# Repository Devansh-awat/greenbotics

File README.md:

|  |
| :----------------------------------------------------------: |

|  |  |
| :----------------------------------------------------------- | -----------------------------------------------------------: |
| Scan QR to open Github repo                                  |                                Scan QR to open YouTube video |

<div style="font-family: Baskerville; font-size: 28px; text-align: center; font-style: italic;">
    This Incredible Repository
</div>

Welcome to the Greenbotics 2025 repository! This repository contains everything we've worked on over the past ten months, including all our code and resources. You can also use this repository as a complete guide to understand and reconstruct the robot from the ground up.

## Table of Contents

- [The Team](#the-team)
- [The Challenge](#the-challenge)
  - [Our Vision](#our-vision)
  - [Skills We Learned](#skills-we-learned)
- [Photos of our Robot](#photos-of-our-robot)
- [Robot Performance Video](#robot-performance-video)
- [Mobility Management](#mobility-management)
  - [Powertrain](#powertrain)
  - [Steering System](#steering-system)
  - [Chassis](#chassis)
  - [Code for mobility components](#code-for-mobility-components)
- [Power and Sense Management](#power-and-sense-management)
  - [LiPo battery](#lipo-battery)
  - [Raspberry Pi](#raspberry-pi)
  - [Voltage Converter](#voltage-converter)
  - [Printed Circuit Board (PCB)](#printed-circuit-board-pcb)
  - [Camera](#camera)
  - [IMU](#imu)
  - [Distance Sensor](#distance-sensor)
  - [Multiplexer](#multiplexer)
  - [Code for sensors](#code-for-sensors)
- [Obstacle Management](#obstacle-management)
  - [Open Challenge Navigation Algorithm](#open-challenge-navigation-algorithm)
    - [Potential improvements in Open Navigation Algorithm](#potential-improvements-in-open-navigation-algorithm)
  - [Obstacle Challenge Navigation Algorithm](#obstacle-challenge-navigation-algorithm)
    - [Potential improvements in Obstacle Navigation Algorithm](#potential-improvements-in-obstacle-navigation-algorithm)
- [Engineering Factors](#engineering-factors)
  - [Design evolution](#design-evolution)
  - [From Nationals to Internationals!](#from-nationals-to-internationals)
- [Robot construction guide](#robot-construction-guide)
  - [1: Print the 3D parts](#1-print-the-3d-parts)
  - [2: Assemble the steering and drive train](#2-assemble-the-steering-and-drive-train)
  - [3: Attach the 3D mounts](#3-attach-the-3d-mounts)
  - [4: Fabricate the PCB](#4-fabricate-the-pcb)
  - [5: Soldering the electronics and gradual safe startup](#5-soldering-the-electronics-and-gradual-safe-startup)
  - [6: Download the code](#6-download-the-code)
  - [7: Robot stability](#7-robot-stability)
- [Major challenges faced](#major-challenges-faced)
- [How we used Github](#how-we-used-github)
- [Bill of Materials](#bill-of-materials)

# The Team

<p style="text-align:center;">Yes. We did know the camera was on!</p>

---

|  | Devansh<br/>Hi! I’m Devansh doing my second WRO season. Last year I represented India in the RoboMission category coming #25 in Internationals. This year I wanted a new challenge and learn new things. My hobbies are coding and robotics. |
| ------------------------------------------------------------ | ------------------------------------------------------------ |
|  | **Sheel**<br/>**Hi! I'm Sheel. I'm 15, and doing my second WRO season. Last year, our team made it to the International Finals in Robomission Junior. Additionally, I'm learning competitive debate. I also have a dog, and both of us are obsessed with Monkeys.** |
|  | **Rakshith**<br/>**I'm Rakshith, a 9th grader passionate about robotics and aspiring to study engineering in Germany. I love building drones, experimenting with sensors. I also have 3 dogs, and two of them live with my grandparents in Hyderabad.** |
|  | **Paresh Gambhava**<br/>**Mr. Paresh Gambhava is our chief coach from The Robotronics Club Ahmedabad. He is a robotics enthusiast, and electrical engineer by profession. He has vast experience training students for Robotics competition and projects.** |

# The Challenge

The [Future Engineer Challenge](https://wro-association.org/wp-content/uploads/WRO-2025-Future-Engineers-Self-Driving-Cars-General-Rules.pdf "View the season rulebook") for the 2025 WRO Season involves building an autonomous vehicle that can complete two challenges. The first challenge is the Open Challenge. This challenge involves the robot completing three full laps on the field. The field consists of outer boundary walls, and 4 inner walls that are randomly placed to form a closed rectangle.

The second challenge is the Obstacle Challenge. In the Obstacle Challenge red or green cuboids called Traffic Signs are placed along the course. The robot must complete three laps around the track while making sure to pass the red traffic signs from the left, and the green traffic signs from the right. The Obstacle Challenge also has a dedicated Parking Space. The robot must start and end in the parking space to attain full points. The walls placement is fixed for the Obstacle Challenge.

## Our Vision

With a deep interest in robotics and programming, the WRO Future engineers challenge was a great opportunity for us to work and build a robot together. We had been seeing other teams in our institute work on this problem last year, and it was greatly motivating for us to see them work. Having represented India in last years WRO RoboMission, we were excited to participate in new category and learn new things.

## Skills We Learned

**Technical Skills:**

- 3D printing and design
- PCB design and creation
- Raspberry Pi programming
- Computer vision and camera programming
- Hardware integration

**Soft Skills:**

- Teamwork
- Problem-solving
- Not go crazy when the robot doesn’t behave as expected !!!

# Photos of our Robot

We designed our robot with Raspberry Pi 5 as the main brain of the car. Raspberry Pi 5 had pre-integrations with the camera allowing us to use faster smarter image procesing algorithms which is critical in this robots design.
Having spent a lot of time working on LEGO-based hardware in the 2024 season, we chose to use many LEGO parts for our Robot's Hardware.  However the robot also uses a Raspberry Pi, Raspberry Pi camera, and other off the shelf electronic components.

|                           Top view                           |                         Bottom view                          |
| :----------------------------------------------------------: | :----------------------------------------------------------: |
|  |  |

|                          Front view                          |                          Rear view                           |
| :----------------------------------------------------------: | :----------------------------------------------------------: |
|  |  |

|                          Left view                           | Right view                                                   |
| :----------------------------------------------------------: | ------------------------------------------------------------ |
|  |  |

# Robot Performance Video

This playlist consists of 3 videos that show our robot's construction, open challenge run as well as obstacle challenge run.

|  |  <br />Scan QR code to open in YouTube |
| ------------------------------------------------------------ | ------------------------------------------------------------ |

---

# Mobility Management

Our robot's mobility system is designed around a LEGO-based chassis that balances ease of assembly with reliable performance. We selected a LEGO EV3 Medium Motor for propulsion due to its compatibility with our modular design approach, delivering 240-250 RPM at 9V through a differential drivetrain that enables smooth turning by allowing wheels to rotate at different speeds. For precise steering control, we integrated an SG90 servo motor with a custom 3D-printed mount that connects to our LEGO chassis. The TB6612FNG motor driver manages power delivery and speed control, while all components are securely mounted to our LEGO framework using standard connectors and custom PCB integration. This design prioritizes modularity and maintainability while providing the torque and precision needed for autonomous navigation challenges.

## Powertrain

### Motor

We chose to use a standard LEGO EV3 Medium Motor, as it easily integrates with the lego chassis and lego axle. This motor also embeds an encoder which could be used if required. However, the standard Lego connector doesn’t directly connect to our motor driver, therefore we identified the pinout of the LEGO motor and directly connected the wires to the motor driver. The pinout diagram of Lego EV3 motor is shown below

---
<table>
  <tr>
    <td width="50%" style="text-align: left;">
      
    </td>
    <td width="50%" style="text-align: left; vertical-align: top;">
      <h3>Specifications:</h3>
      <li>Name: LEGO EV3 Motor</li>
      <li>Voltage: 9V</li>
      <li>No Load Speed: 240 to 250 RPM</li>
      <li>Weight: 40g</li>
      <li>Encoder resolution: 1°</li>
    </td>
  </tr>
</table>

---

**Potential improvements:**

- Use the built-in encoder for more accurate movement and turns of the robot. Using the encoder allows for precise and accurate movements, helping in complex tasks like parking.

- Consider exploring more powerful non-Lego geared motors that are

    -Compact and lightweight

    -More powerful

    -Cheaper

### Drivetrain

Our EV3 motor is connected to a Lego axle that drives a gear connected to a Lego differential, which splits torque between two wheels. The differential lets both wheels rotate at different speeds when turning, thereby reducing the friction at each wheel, and making turns smoother. We used lego wheels as they are compatible with lego axle used for the chassis. We experimented with a wide variety of Lego wheels for the robot. Increasing the size of the rear wheel increased the robot speed almost linearly proportional to the wheel diameter. Increasing the width of the front tyres caused the robot to skid during turns, hence the front wheels are narrower to make smooth turns. The rear wheels are wider to provide sufficient friction to the vehicle.

**Potential Improvements**

- Explore alternative differential gear mechanisms to avoid the wheels slipping, especially on the smooth surface of the mat.
- Explore options for front wheels with vertical treads as the Lego narrow wheels do not have tread.

### Motor Driver

To control the current received by the motor and to control the speed of the drive motor, we utilized a SparkFun Dual TB6612FNG motor driver. The motor driver is connected to our PCB, and receives signals from the Raspberry Pi.

<table>
  <tr>
    <td width="50%" style="text-align: left;">
      
    </td>
    <td width="50%" style="text-align: left; vertical-align: top;">
      <h3>Specifications:</h3>
      <li>Name: TB6612FNG</li>
      <li>Power Supply Voltage: 15V (Max)</li>
      <li>Average Output current: 1.2A</li>
      <li>Peak Output current: 3.2A</li>
      <li>Standby control to save power</li>
      <li>Built-in thermal shutdown circuit</li>
    </td>
  </tr>
</table>

**Potential Improvements:**

- Explore motor driver that can output higher currents, if we upgrade existing motors to higher performance motors

## Steering System

For our steering mechanism, we needed a design that was precise. Like all other aspects of our robot’s design, our first choice was to use a Lego based mechanism. Ackerman steering is a popular choice in automobiles, as the front inner wheel turns more than the front outer wheel, thereby reducing skid. However it was complicated to build it. We first tried the simpler parallel steering mechanism and it turned out to be pretty good for our robot, so we didn't consider Ackerman steering.

The steering could have been driven by any encoder based motor (such as a spike prime small motor) as a makeshift servo motor. The problem was, that while any Lego motor would have been both highly precise and easy to integrate, even the smallest motor was too bulky and required integration with motor driver.

Therefore, we decided to use an off the shelf servo motor, which was not only small but can be driven directly by Raspberry Pi's output port. To integrate it with our Lego based design, we 3D printed a custom servo mount which could be attached with Lego screws to the front of the chassis directly behind the front wheel, while simultaneously hot gluing the servo horn to 3D printed component that couples the horn to the axle of the front wheels.

**Potential Improvements:**

- Explore if Ackerman steering provides better maneuverability.

### Servo Motor

Our steering system is centered around the SG90 servo motor, which provides precise angular control, making it highly suitable for steering applications where accuracy is essential. Unlike standard DC motors, the SG90 has a built-in feedback mechanism that allows it to hold a commanded angle reliably without additional sensors. Despite its compact size, it delivers sufficient torque to handle the demands of turning the steering mechanism, ensuring stability.

<table>
  <tr>
    <td width="50%" style="text-align: left;">
      
    </td>
    <td width="50%" style="text-align: left; vertical-align: top;">
      <h3>Specifications:</h3>
      <li>Name: SG90</li>
      <li>Operating voltage: 3.0V - 7.2V</li>
      <li>Weight: 9g</li>
    </td>
  </tr>
</table>

<table>
  <tr>
    <td width="50%" style="text-align: left;">
      
    </td>
    <td width="50%" style="text-align: left; vertical-align: top;">
      <h3>Servo mount</h3>
      <li>To connect the servo motor to our robot, we designed and 3D printed a custom Servo Mount</li>
      <li>A diagram of our servo mount is shown to the left.</li>
      <li>A 3D Printable file is provided in the models folder.</li>
    </td>
  </tr>
</table>

**Challenges:**

For a brief period, we used an MG90 servo motor instead of our current SG90 motor. An MG90 has metal gears instead of plastic gears, which we believed would make it more reliable. However, the MG90 gears broke in one of our test runs, and we reverted back to the SG90

**Potential Improvements:**

- 3D print the servo horn to directly connect to the chassis without gluing

## Chassis

When starting this project, we realized that the bulk of our effort would go into building autonomous driving software. As we wanted to spend more time on software, and had already spent a considerable amount of time using Lego hardware for our 2024 Robomission challenge, we **custom designed** the base chassis from elementary Lego parts and rest of the chassis with **3D printed parts**.

This approach has many benefits, the primary one being ease of integration. Lego parts can easily be snapped on and off, making chassis development far easier and less time consuming. Making changes to a non-Lego chassis would have meant that each time we wanted to make a change to our chassis, we would have to make new 3D prints, increasing time, cost, waste and materials used.

All sensors like the camera, ultrasonic sensors and TOF sensors are attached to the base chassis with 3D printed mounts. This provides robust attachment of the the sensors to the main body. The prototype was built with hot gluing these sensors to the body but this wasn't robust and would come off.

|  |  |
| ------------------------------------------------------------ | ------------------------------------------------------------ |
|  |  |

|  |
| :----------------------------------------------------------: |

**Potential Improvements:**

- Despite being mounted on a thick 3D-printed mount, the camera vibrates when the robot is in motion, blurring the image. The mount could be coupled with vibration damping material.
- Lightweight suspension can be added to the chassis to enhance stability.
- The Raspberry Pi's cooling fan can be covered with a custom 3D printed cover to avoid dust and debris getting into the fan.
- The current 3D printed parts are printed with 100% infill for robustness but it increases the weight. We could explore an optimum infill that gives the minimum strength at the lowest possible weight.

## Code for mobility components

### Motor Control

Controls the drive motor speed and direction using PWM (pulse-width modulation) signals sent to the TB6612FNG motor driver.

#### Initialization

```python
def initialize():
    """Initializes the DC motor driver and PWM."""
    global gpio_handle, motor_pwm
    try:
        gpio_handle = lgpio.gpiochip_open(0)
        lgpio.gpio_claim_output(gpio_handle, config.AIN1_PIN)
        lgpio.gpio_claim_output(gpio_handle, config.AIN2_PIN)
        lgpio.gpio_claim_output(gpio_handle, config.STBY_PIN)
        
        motor_pwm = HardwarePWM(
            pwm_channel=config.MOTOR_PWM_CHANNEL,
            hz=config.MOTOR_PWM_FREQ,
            chip=config.MOTOR_PWM_CHIP,
        )
        motor_pwm.start(0)
        print("INFO: Motor Initialized.")
        return True
    except Exception as err:
        print(f"FATAL: Motor failed to initialize: {err}")
        return False
```

**Explanation:** We set up the GPIO pins that control the motor direction (AIN1, AIN2) and standby mode (STBY). We also initialize the PWM signal that controls motor speed.

#### Motor Control Functions

```python
def forward(speed):
    """Drives the motor forward at a given speed."""
    if gpio_handle:
        lgpio.gpio_write(gpio_handle, config.STBY_PIN, 1)  # Enable motor
        lgpio.gpio_write(gpio_handle, config.AIN1_PIN, 1)  # Forward direction
        lgpio.gpio_write(gpio_handle, config.AIN2_PIN, 0)
        _set_speed(speed)  # Set speed 0-100

def reverse(speed):
    """Drives the motor in reverse at a given speed."""
    if gpio_handle:
        lgpio.gpio_write(gpio_handle, config.STBY_PIN, 1)  # Enable motor
        lgpio.gpio_write(gpio_handle, config.AIN1_PIN, 0)  # Reverse direction
        lgpio.gpio_write(gpio_handle, config.AIN2_PIN, 1)
        _set_speed(speed)

def brake():
    """Brakes the motor by shorting its terminals."""
    if gpio_handle:
        lgpio.gpio_write(gpio_handle, config.STBY_PIN, 1)
        lgpio.gpio_write(gpio_handle, config.AIN1_PIN, 1)  # Both pins high = brake
        lgpio.gpio_write(gpio_handle, config.AIN2_PIN, 1)
        _set_speed(0)
```

**Explanation:** These functions control motor direction by setting the AIN1 and AIN2 pins. Forward sets AIN1=1 and AIN2=0. Reverse does the opposite. Brake sets both to 1, which stops the motor quickly.

---

### Servo Steering

Controls the steering servo angle using PWM signals. The servo position determines the steering direction.

#### Initialization

```python
def initialize():
    """Initializes the servo motor PWM."""
    global servo_pwm
    
    for attempt in range(1, 6):  # Try up to 5 times
        try:
            servo_pwm = HardwarePWM(
                pwm_channel=config.SERVO_PWM_CHANNEL,
                hz=config.SERVO_PWM_FREQ,
                chip=config.SERVO_PWM_CHIP,
            )
            servo_pwm.start(0)
            set_angle(0.0)  # Center the servo
            time.sleep(0.5)
            print("INFO: Servo Initialized.")
            return True
        except PermissionError as err:
            print(f"WARNING: Servo PWM permission denied (attempt {attempt}/5): {err}")
            time.sleep(0.1 * attempt)
    
    print("FATAL: Servo failed to initialize after 5 attempts")
    return False
```

**Explanation:** We initialize the PWM signal for the servo. The servo needs a specific frequency (50 Hz) and pulse width to set its angle. We center it at 0 degrees during startup.

#### Servo Angle Control

```python
def set_angle(input_angle: float):
    """Sets the servo to a specific angle (-45 to +45 degrees)."""
    if servo_pwm is None:
        return
    
    # Clamp angle to safe limits
    clamped_angle = max(-45, min(45, input_angle))
    
    # Convert angle to PWM duty cycle
    # Servo expects 1-2ms pulse width at 50Hz frequency
    pulse_width_ms = 1.5 + (clamped_angle / 90) * 0.5
    duty_cycle = (pulse_width_ms / 20) * 100
    
    servo_pwm.change_duty_cycle(duty_cycle)
```

**Explanation:** Servo motors work by receiving a PWM signal with a specific pulse width. A 1.5ms pulse = center (0°), 1ms = full left (-90°), 2ms = full right (+90°). We calculate the duty cycle based on the desired angle.

# Power and Sense Management

Our robot uses a Raspberry Pi 5 to process data from several sensors. We use ultrasonic and TOF sensors for distance, an IMU for orientation, and a camera for autonomous driving. A Li-Po battery powers the entire system.

## LiPo battery

Our robot uses a Bonka 11.1V 2200mAh LiPo battery, commonly found in drones and quadcopters. We chose this battery because its compact form factor fits in the narrow space beneath the chassis. Mounting the heavy battery low in the robot lowers the center of mass, which improves stability.

<table>
  <tr>
    <td width="50%" style="text-align: left;">
      
    </td>
    <td width="50%" style="text-align: left; vertical-align: top;">
      <h3>Specifications:</h3>
      <li>Maximum Voltage: 12.6V </li>
      <li>Nominal Voltage: 11.1V </li>
      <li>Capacity: 2200mAh</li>
      <li>Discharge Current: 35C</li>
      <li>Weight: 175g</li>
    </td>
  </tr>
</table>

---
**Potential Improvements**

- Implement a battery level indicator
- Explore if a Lithium-Ion battery is available in the required form factor, as it

    - Is safer

    - Has more charge cycles

    - Doesn't require a complex charger that a LiPo requires
    
    - Can be easily removed and replaced with another charged battery
---
## Raspberry Pi

The heart of our robot is the Raspberry Pi 5 microcomputer. It processes inputs from our distance sensors, runs image processing algorithms on the live camera feed and controls the motors to drive the robot to achieve its desired goals.

We chose this particular model as it seamlessly integrates with a camera, making it easier to use than similar computers or microcontrollers such as an Arduino or ESP32. Additionally, we also wanted to take advantage of the Raspberry Pi 5 being far more powerful than other processors, allowing us to use newer and improved image processing technologies that deliver more accurate results but may require greater computing power.

**Potential Improvements**

- Use Arduinos and compatible cameras to make this robot much cheaper to design

<table>
  <tr>
    <td width="50%" style="text-align: left;">
      
    </td>
    <td width="50%" style="text-align: left; vertical-align: top;">
      <h3>Specifications:</h3>
      <li>Name: Raspberry Pi 5 </li>
      <li>RAM: 8GB</li>
      <li>Pins: 40</li>
      <li>Input Voltage: 5V</li>
    </td>
  </tr>
</table>

## Voltage Converter

Our battery provides 12V, but our Raspberry Pi requires 5V and our motor requires 9V. To supply these lower voltages safely, we used a XY-3606 step-down (buck) voltage converter.

**Potential Improvements**

- Use a linear converter to reduce costs
- Use a buck converter that is more efficient and provides more power at different voltages. This ensures that all components running at all voltages can be used

<table>
  <tr>
    <td width="50%" style="text-align: left;">
      
    </td>
    <td width="50%" style="text-align: left; vertical-align: top;">
      <h3>Specifications:</h3>
      <li>Name: XY-3606 </li>
      <li>Working voltage: DC 9V–36V</li>
      <li>Output voltage: 5.2V</li>
    </td>
  </tr>
</table>

## Printed Circuit Board (PCB)

In our first draft of the robot, there were many criss-crossing wires between many different components. A lack of clean arrangement for the wires made the robot very messy to handle. During practice runs, wires would routinely get loose, making it difficult to troubleshoot errors.

To solve this, we designed a PCB which cleanly connected all of our components together, making the robot far cleaner and reliable.

Here is a comparison showing our robot before and after the PCB

| Before                                                       | After                                                        |
| ------------------------------------------------------------ | ------------------------------------------------------------ |
|  |  |

<table>
  <tr>
    <td width="50%" style="text-align: left;">
      
    </td>
    <td width="50%" style="text-align: left; vertical-align: top;">
      <h3>PCB</h3>
      <li>This is our PCB image with all components mounted</li>
      <li>The 'models/PCB' folder contains the files required to print this PCB</li>
    </td>
  </tr>
</table>

## Camera

For image detection, we are using the Raspberry Pi Camera Module 3. This uses a CMOS sensor, the Sony IMX708. Apart from its ease of integration with the Raspberry Pi, the Camera module 3 has autofocus, wide-angle and low-light performance, all of which are very useful in a competition setting.

We explored few other alternatives as well. The Raspberry Pi AI camera provides built in detection for many objects, but has a limited Field Of View which didn't work for our requirements. The Raspberry Pi HQ camera though bulky comes with a standard CS mount that allowed us to mount different fish eye lenses. A fish eye lens camera provides a much larger Field Of View (160° - 180°) even when mounted in the front on a straight mount at 10cm height. This allows us to cut off the field view above the black walls making the robot resilient to off field objects. However the image is distorted towards the edges and tuning the robot to detect objects proved difficult for us.

<table>
  <tr>
    <td width="50%" style="text-align: left;">
      
    </td>
    <td width="50%" style="text-align: left; vertical-align: top;">
      <h3>Specifications:</h3>
      <li>Name: Camera Module 3 </li>
      <li>Resolution: 11.9 megapixels</li>
      <li>Horizontal/vertical: 4608 × 2592 pixels</li>
      <li>Autofocus, Wide-angle and Low-light performance</li>
    </td>
  </tr>
</table>

**Potential Improvements**

- Use an alternative wide angle AI camera to process data on the camera itself. This will reduce processing load on the Raspberry Pi.
- Attempt to resolve tuning issues with fish eye camera to ignore off field objects.

## IMU

Our robot uses the BNO055 IMU (Inertial Measurement Unit) to help it maintain direction when moving straight, and to make turns more accurate. The BNO055 combines data from an accelerometer, gyroscope, and magnetometer to provide absolute orientation, which reduces drift and allows the robot to correct its heading in real time.

<table>
  <tr>
    <td width="50%" style="text-align: left;">
      
    </td>
    <td width="50%" style="text-align: left; vertical-align: top;">
      <h3>Specifications:</h3>
      <li>I2C Address: 0x28 </li>
      <li>Gyroscope: Range ±125°/s to ±2000°/s</li>
      <li>Accelerometer: Range ±2g, ±4g, ±8g, ±16g</li>
    </td>
  </tr>
</table>

**Potential Improvements**

- Move the IMU away from areas of magnetic interference
- Use higher quality IMUs such as the BNO085

## Distance Sensor

Apart from the camera, our robot uses TOF based distance sensors VL53L1X / VL53L8CX and URM09 Ultrasonic sensor to gather inputs. The sensors are mounted on the front, back, left, and right of the robot respectively. The front and back sensors are used to avoid hitting the parking walls. The left and right sensors are used to detect the starting direction for obstacle challenge. They could potentially be used for a surprise rule that may be announced at the competition.

**Reasons for using different sensors**

- Ultrasonic sensors are not affected by strong lighting at competition arenas and are useful to detect objects at larger distance. This is useful for wall detection.
- Some TOF sensors could potentially be affected by strong lighting at competition arenas, but are usually safe over short distances. This is useful for parking.
  - The back sensor is attached to the edge of the rear chassis hence requires min 2cm range.
  - The front sensor is attached to the inner cavity behind the front wheels hence can work with 4cm range.

<table>
  <tr>
    <td width="50%" style="text-align: left;">
      
    </td>
    <td width="50%" style="text-align: left; vertical-align: top;">
      <h3>VL53L1X Specifications:</h3>
      <li>Operating Voltage: 3.3V </li>
      <li>Range: 4cm to 4m</li>
      <li>Resolution: 1mm</li>
    </td>
  </tr>
  <tr>
    <td width="50%" style="text-align: left;">
      
    </td>
    <td width="50%" style="text-align: left; vertical-align: top;">
      <h3>VL53L8CX Specifications:</h3>
      <li>Operating Voltage: 3.2V to 5.5V </li>
      <li>Range: 2cm to 4m</li>
      <li>Resolution: 1mm</li>
    </td>
  </tr>  
  <tr>
    <td width="50%" style="text-align: left;">
      
    </td>
    <td width="50%" style="text-align: left; vertical-align: top;">
      <h3>URM09 Specifications:</h3>
      <li>Operating Voltage: 3.3V to 5.5V</li>
      <li>Range: 2cm to 5m</li>
      <li>Resolution: 1cm</li>
    </td>
  </tr>
</table>

**Alternatives considered**

Along with the Ultrasonic and VL53L1X sensors, we also considered LiDAR sensors to help map the game field. In the end, though, we decided to pass on this, as LiDAR sensors are too expensive. Adding a single LiDAR sensor could have increased the robot's cost by nearly 40%. Additionally, at the short ranges relevant to this game field, our existing ultrasonic and ToF sensors already provide sufficient accuracy, so LiDAR would not have meaningfully improved the robot’s accuracy.

**Potential Improvements**

- Use a lidar sensor for a complete 2D image of the surroundings

## Multiplexer

All four of our distance sensors share the same I²C address. Our CJMCU TCA9548A multiplexer splits the  distance sensors into separate channels so only one device is active at a time. This gives each device a “virtual” unique address, letting them coexist without conflict.

<table>
  <tr>
    <td width="50%" style="text-align: left;">
      
    </td>
    <td width="50%" style="text-align: left; vertical-align: top;">
      <h3>Specifications:</h3>
      <li>Model Number: CJMCU TCA9548A </li>
      <li>No. of Channels: 8 </li>
    </td>
  </tr>
</table>

## Bringing it all together

**A full wiring diagram is shown in the screenshot below, and available at models/PCB/~Untitled.kicad_sch**

## Code for sensors

### IMU (Gyroscope) - BNO055

Measures the robot's heading (direction) using a combination of gyroscope, accelerometer, and magnetometer sensors.

#### Initialization

```python
def initialize():
    """Initializes the BNO055 sensor."""
    global sensor
    
    try:
        i2c = board.I2C()
        sensor = adafruit_bno055.BNO055_I2C(i2c)
        sensor.mode = adafruit_bno055.NDOF_MODE  # 9-DOF mode
        time.sleep(1)  # Let sensor boot up
        
        print(f"INFO: Gyro (BNO055) Initialized. Temp: {sensor.temperature}°C")
        print(f"INFO: Calibration status: {sensor.calibration_status}")
        return True
    except Exception as e:
        print(f"WARNING: Gyro disabled. Could not initialize: {e}")
        sensor = None
        return True
```

**Explanation:** We initialize the BNO055 on the I2C bus and set it to NDOF mode (9-Degree of Freedom), which uses all three sensors together for accurate heading measurement.

#### Reading Heading

```python
def get_heading():
    """Returns the current heading (yaw) in degrees."""
    if sensor:
        try:
            heading, _, _ = sensor.euler  # Get yaw (heading) from Euler angles
            if heading is not None:
                return heading
        except Exception:
            return None
    return None

def get_initial_heading(num_readings=20):
    """Gets an averaged, stable initial heading."""
    if not sensor:
        return 0.0
    
    print("INFO: Acquiring initial heading...")
    readings = []
    for _ in range(num_readings):
        yaw = get_heading()
        if yaw is not None:
            readings.append(yaw)
        time.sleep(0.05)
    
    if readings:
        initial_heading = np.mean(readings)
        print(f"INFO: Gyro zero point set to: {initial_heading:.2f} degrees.")
        return initial_heading
    return 0.0
```

**Explanation:** The BNO055 returns Euler angles (heading, roll, pitch). We extract the heading (yaw) which tells us which direction the robot is facing. We average multiple readings at startup to get a stable initial heading.

---

### Camera - Raspberry Pi Camera Module 3

Captures video frames for obstacle detection and color identification using computer vision.

#### Initialization

```python
def initialize():
    """Initializes the Picamera2."""
    global picam2
    try:
        picam2 = Picamera2()
        cam_config = picam2.create_preview_configuration(
            main={
                "format": "RGB888",
                "size": (2304, 1296),  # High resolution for processing
            },
            lores={
                "size": (640, 360),    # Low resolution for fast processing
                "format": "RGB888"
            },
            controls={
                "ExposureTime": 8000,  # Exposure time in microseconds
                "FrameRate": 56,       # Frames per second
            }
        )
        picam2.configure(cam_config)
        picam2.start()
        time.sleep(1.0)
        print("INFO: Camera Initialized.")
        return True
    except Exception as e:
        print(f"FATAL: Camera failed to initialize: {e}")
        return False
```

**Explanation:** We set up the camera with two resolutions: high resolution (2304×1296) for detailed processing and low resolution (640×360) for fast real-time processing. We also set exposure time and frame rate for consistent image quality.

#### Capturing Frames

```python
def capture_frame():
    """Captures and returns a single frame from the camera."""
    if picam2:
        frame = picam2.capture_array("lores")  # Get low-res frame for speed
        return frame
    return None
```

**Explanation:** We capture frames from the low-resolution stream for fast processing. This lets us run obstacle detection at 30 FPS without slowing down the robot.

### Distance Sensors - VL53L1X

Measures distance to walls and obstacles using time-of-flight (ToF) technology. Four sensors are mounted on the front, back, left, and right.

#### Initialization

```python
def initialise():
    """Initializes the I2C bus, multiplexer, and all distance sensors."""
    global _i2c_main, _mux, _sensors, _sensor_types
    
    try:
        _i2c_main = busio.I2C(board.SCL, board.SDA)
    except Exception as e:
        print(f"FATAL: Could not initialize I2C bus. Error: {e}")
        return False
    
    try:
        _mux = adafruit_tca9548a.TCA9548A(_i2c_main, address=0x70)
        print("INFO: TCA9548A Mux found at address 0x70.")
    except ValueError:
        print("WARNING: TCA9548A Mux not found.")
        _mux = None
    
    # Probe each channel for sensors
    if _mux:
        print("INFO: Probing for sensors on mux channels...")
        for i in range(8):
            channel_bus = _mux[i]
            
            try:
                vl53_sensor = adafruit_vl53l1x.VL53L1X(channel_bus)
                vl53_sensor.distance_mode = 1
                vl53_sensor.timing_budget = 50
                vl53_sensor.start_ranging()
                _sensors[i] = vl53_sensor
                _sensor_types[i] = 'VL53L1X'
                print(f"  - SUCCESS: VL53L1X found on channel {i}.")
            except (ValueError, OSError):
                print(f"  - INFO: No sensor found on channel {i}.")
    
    print("INFO: Sensor initialization complete.")
    return True
```

**Explanation:** We initialize the I2C bus and the TCA9548A multiplexer. The multiplexer lets us connect 4 sensors with the same I2C address by switching between channels. We probe each channel and initialize any VL53L1X sensors we find.

#### Reading Distance

```python
def get_distance(channel):
    """Reads the distance from a sensor on a specific channel."""
    if channel not in _sensors:
        return None
    
    sensor = _sensors[channel]
    
    try:
        if sensor.data_ready:  # Check if new data is available
            distance_cm = sensor.distance
            sensor.clear_interrupt()
            return distance_cm * 10.0 if distance_cm is not None else None
        return None  # No new data yet
    except (OSError, IOError):
        print(f"I/O Error on channel {channel}. Sensor may be disconnected.")
        return None
```

**Explanation:** We check if the sensor has new data ready. If it does, we read the distance in centimeters and convert it to millimeters. If no new data is ready, we return None immediately without blocking.

# Obstacle Management

## Open Challenge Navigation Algorithm

Navigate 3 laps using camera-based wall detection steering straight in the straight sections. Steer according to the driving section in the corner section. Count turns using orange lines. Stop after 12 turns.

### How it works

1. Detect black walls using HSV color masks
2. Calculate left vs right wall area
3. Steer toward bigger wall (proportional steering)
4. Detect orange lines for turn counting
5. Execute sharp turns when close wall detected
6. Stop after 12 turns

### Flowchart

### Steering

- Calculate difference between two wall areas
- If one side wall disappears, means we are in a turn, turn sharply towards the other side
- Otherwise turn with regular Kp=0.0005

#### Code

```python
left_pixel_size = sum(obj['area'] for obj in detected_walls if 'left' in obj['type'])
right_pixel_size = sum(obj['area'] for obj in detected_walls if 'right' in obj['type'])

# If one side wall disappears, turn sharply towards the other side
if left_pixel_size < 100 and right_pixel_size > 100:
    right_pixel_size += 25000
elif right_pixel_size < 100 and left_pixel_size > 100:
    left_pixel_size += 25000
              
angle = ((left_pixel_size - right_pixel_size) * 0.0005)
```

### Turn Counting
- Detect orange lines in specific ROI
- Keep history of last 4 frames
- Increment counter on no line → line transition
- Use 50-frame cooldown to prevent double-counting

#### Code

```python
orange_detection_history = deque([False] * 4, maxlen=4)
cooldown_frames = 0
orange_detected_this_frame = bool(detections['detected_orange'])
orange_detection_history.append(orange_detected_this_frame)

if cooldown_frames > 0:
    cooldown_frames -= 1
elif not orange_detection_history[-4] and all(list(orange_detection_history)[1:]):
    turn_counter += 1
    cooldown_frames = 50
```

### Sharp Turn Detection
- If close wall area > 3000 pixels: execute sharp turn
- Angle = ±35 degrees
- Prevents collision

#### Code

```python
close_black_area = sum(obj['area'] for obj in detections.get('detected_close_black', []))
if close_black_area > 3000:
    if left_pixel_size < right_pixel_size:
        angle = -35
    else:
        angle = 35
```

### Potential improvements in Open Navigation Algorithm

- Instead of driving in the center of the lane, drive towards the inner wall which could reduce time further. This requires careful tuning of the turns to avoid hitting the walls.

## Obstacle Challenge Navigation Algorithm

Navigate 3 laps while avoiding colored blocks. Drive left of the green block and right of the red block. Detect the driving direction automatically. Count turns using orange lines. Avoid the magenta parking blocks in all laps. Execute parallel parking just before the vehicle approaches the 13th orange line.

### How it works

1. Detect driving direction (clockwise vs counter-clockwise)
2. Perform initial maneuver (85° turn with scanning)
3. Navigate main loop with block avoidance
4. Count turns using orange/blue lines
5. Execute parking at turn 13

### Flowchart

### Driving Direction Detection

1. Compare left vs right distance sensor readings
2. If left < right: clockwise
3. If right < left: counter-clockwise

#### Code

```python
dist_left = sensor_thread.get_readings()['distance_left']
dist_right = sensor_thread.get_readings()['distance_right']

if dist_left is not None and dist_right is not None:
    if dist_left < dist_right:
        driving_direction = "clockwise"
    else:
        driving_direction = "counter-clockwise"
```

### Initial maneuver

This is the logic for counter clockwise. The logic for clockwise would be mirrored

1. Head out of the parking in slanted orientation
2. scan for blocks (1 second)
3. If red block: reverse and take a right turn
4. If green block: drive forward and take a right turn
5. If no block: drive slanted 1s
6. Return to main loop

#### Flowchart

#### Code

```python
SCAN_TRIGGER_ANGLE_DEG = 25.0
TOTAL_TURN_ANGLE_DEG = 85.0

motor.forward(MANEUVER_SPEED)
servo.set_angle_unlimited(initial_turn_servo)

while get_angular_difference((INITIAL_HEADING+SCAN_TRIGGER_ANGLE_DEG)%360, 
                             imu_thread.get_heading()) > 10:
    time.sleep(0.01)

motor.brake()
# Scan for blocks
detected_block_color = None
scan_start_time = time.monotonic()

while time.monotonic() - scan_start_time < 1.0:
    frame, frame_counter = camera_thread.get_frame()
    if frame is None: continue
    detections = process_video_frame(frame)
    main_blocks = [b for b in detections.get('detected_blocks', []) if b['type'] == 'block']
    
    if main_blocks and main_blocks[0]['area'] > 1000:
        detected_block_color = main_blocks[0]['color']
        break
```

### **Color Detection**

Detect 6 different colors to identify walls, blocks, turn lines, and parking boundaries. Each color serves a specific purpose in navigation and obstacle avoidance.

1. Convert frame to HSV color space
2. Apply Gaussian blur
3. Create masks for each color
4. Apply ROI masks (region of interest)
5. Find contours (outlines)
6. Filter by minimum area
7. Calculate centroid (center point)

#### Flowchart

#### Code

```python
def process_video_frame(frame):
    hsv_frame = cv2.cvtColor(frame, cv2.COLOR_BGR2HSV)
    
    mask_red1 = cv2.inRange(hsv_frame, [0, 150, 80], [10, 255, 255])
    mask_red2 = cv2.inRange(hsv_frame, [175, 150, 80], [180, 255, 255])
    mask_red = cv2.bitwise_or(mask_red1, mask_red2)
    
    mask_green = cv2.inRange(hsv_frame, [36, 50, 70], [89, 255, 255])
    mask_orange = cv2.inRange(hsv_frame, [6, 70, 20], [26, 255, 255])
    mask_magenta = cv2.inRange(hsv_frame, [158, 73, 64], [173, 255, 223])
    mask_blue = cv2.inRange(hsv_frame, [94, 45, 58], [140, 226, 185])
    
    # Apply ROI masks and find contours
    # ... contour detection logic
```

### Regions of Interest

**Why multiple ROIs?**

- Faster processing (less data)
- More accurate (fewer false detections)
- Better performance (40 FPS maintained)

#### 7 ROI Masks

1. **Left Wall ROI** - Detect left wall for steering
2. **Right Wall ROI** - Detect right wall for steering
3. **Inner Left Wall ROI** - Detect inner walls
4. **Inner Right Wall ROI** - Detect inner walls
5. **Main Block ROI** - Detect red/green blocks ahead
6. **Close Block ROI** - Detect blocks very close (emergency)
7. **Line ROI** - Detect orange/blue lines for turns

### Block avoidance

Detect colored blocks (red and green) and execute appropriate maneuvers to avoid them. Handle both emergency situations (very close blocks) and normal avoidance (blocks ahead).

**Close Blocks (Emergency Reverse):**

- Very close to robot
- Execute emergency maneuver: reverse, turn servo, drive forward

**Main Blocks (Steering Avoidance):**
- Ahead of robot but not too close
- Calculate steering to pass correctly:
  - Red: pass from right side
  - Green: pass from left side

#### Flowchart

#### Code

```python
if detected_blocks:
    is_close_block = False
    for block in detected_blocks:
        if block['type'] == 'close_block':
            is_close_block = True
            if block['color'] == 'red':
                angle = -25
            elif block['color'] == 'green':
                angle = 30
            servo.set_angle(angle)
            motor.reverse(60)
            time.sleep(0.5)
            motor.forward(60)
            servo.set_angle(-angle)
            time.sleep(0.3)
            motor.forward(MOTOR_SPEED)
            break
    
    if not is_close_block:
        block = detected_blocks[0]
        block_color = block['color']
        block_x, block_y = block['centroid']
        
        if block_color == 'red':
            target = 150
            angle = ((block_x - (320 - target)) * 0.09) + 1
        elif block_color == 'green':
            target = 150
            angle = ((block_x - (320 + target)) * 0.1) + 1
```

### Parking logic

Execute parallel parking maneuver in two directions (clockwise and counter-clockwise). Use wall following and magenta block detection to position robot precisely at the parking start point. Then execute a parking maneuver to park parallely between parking boundaries.

1. Drive forward until front sensor close to wall
2. Reverse until back sensor close to wall
3. Drive forward taking a left turn entering the parking section
4. Line following mode by tracking black wall on left side at fixed pixel
5. Stop at the second magenta block
6. Park parallelly with the help of IMU and servo

#### Sketch

### Threading Architecture

Threading allows the robot to process multiple tasks simultaneously:
- Capture camera frames
- Read gyro heading
- Read distance sensors
- Write video to file
- Control motors

#### 4 Threads

**CameraThread:**

- Continuously captures frames (~30 FPS)
- Stores latest frame in memory
- Main loop reads this frame

**ImuThread:**
- Continuously reads gyro heading (~100 Hz)
- Stores latest heading in memory
- Main loop reads this heading

**SensorThread:**
- Continuously reads distance sensors (~50 Hz)
- Stores latest readings in memory
- Main loop reads these readings

**VideoWriterThread:**
- Continuously writes frames to MP4
- Receives frames from main loop
- Writes to disk in background

#### Thread Synchronization
Use locks (mutexes) to prevent simultaneous access to shared data. Only one thread can access data at a time.

### Potential improvements in Obstacle Navigation Algorithm

- Experiment with LAB color detection if it resolves some of the color detection problems we face with HSV
- Use Machine Learning to train a model for navigating around parking blocks within the walls and use this model to drive the robot.
- Use Machine Learning to train a model for parallel parking and use it to park the robot
- Use encoder (instead of time based driving) to park more accurately during parallel parking.

# Engineering Factors

## Design evolution

We started building the robot in mid of January 2025 and here is a timeline of our robot evolution over the last 10 months!

1. We designed our own robot chassis with differential gear axle and steering

   |  |  |
   | ------------------------------------------------------------ | ------------------------------------------------------------ |

2. First prototype of motor attachment with vertical orientation secured by zip ties

   |  |
   | :----------------------------------------------------------: |

3. 3D printed assembly to attach servo motor to steering

   |  |
   | :----------------------------------------------------------: |

4. Mounted Raspberry Pi5 on a cardboad sheet, battery, power converter, axle motor, motor driver and servo motor for steering

   |  |
   | :----------------------------------------------------------: |

5. Adding a camera so that our robot can see!

   |  |
   | :----------------------------------------------------------: |

6. Moving the components to a lego base plate to make it more stable

   |  |
   | :----------------------------------------------------------: |

7. Attaching the lego base plate to the robot chassis along with distance sensors

   |  |
   | :----------------------------------------------------------: |

8. All components connected with wires and bread board power rail for electrical prototyping

   |  |
   | :----------------------------------------------------------: |

9. A jungle of wires!

   |  |  |
   | ------------------------------------------------------------ | ------------------------------------------------------------ |

10. Tied the wires neatly and upgraded the sensors

    |  |      |
    | :----------------------------------------------------------: | ---- |

11. Created a custom PCB to solve the wire mess and to make the connections reliable

    |  |  |
    | ------------------------------------------------------------ | ------------------------------------------------------------ |
    |  |  |

12. Moved to a custom PCB

    |  |  |
    | ------------------------------------------------------------ | ------------------------------------------------------------ |

13. Aligned the battery so that it doesn't protrude outside the robot

    |  |
    | :----------------------------------------------------------: |

## From Nationals to Internationals!

- Changed the driving logic from basic object color detection to consider X axis position of the object, resulting in human like driving
-  Used camera to drive between the walls instead of relying on sensors.
-  Designed custom 3D printed mounts for camera, sensors and servo horn.

|  |  |
| ------------------------------------------------------------ | ------------------------------------------------------------ |
| Changed the wheels and designed a custom 3D printed camera mount. Moved the camera to vehicle rear to improve FOV. | Designed a custom 3D printed sensor mount for stable mounting of distance sensors. Designed a 3D printed horn coupling for servo motor. |

# Robot construction guide

## 1: Print the 3D parts
- The STL part files for the mounts for servo motor, servo horn, camera base, camera arm and sensors are in the `models/chassis` folder. Recommended settings
  - Material: PLA
  - Infill: 100%

## 2: Assemble the steering and drive train
- Create the steering assembly using the Lego parts in the photos
- Attach the two rear wheels with a differential gear assembly using Lego gears and axle
- Attach the Lego EV3 medium motor with Lego pins to the chassis
- The Lego motor gears should mesh with the differential gear
- Attach the front wheels

|  |  |  |
| :----------------------------------------------------------- | ------------------------------------------------------------ | ------------------------------------------------------------ |

## 3: Attach the 3D mounts
- Mount the servo on the 3D printed servo motor mount
- Attach the servo horn to the steering with 3D printed servo horn mount
- Attach the servo mount to the chassis using Lego pins
- Attach the Camera base mount to the rear part of the chassis
- Attach the Camera arm mount to the base mount using screws
- Use zip ties if necessary

## 4: Fabricate the PCB
- Fabricate the PCB from the KiCAD files in the `models/PCB` folder using KiCAD (https://www.kicad.org/)
## 5: Soldering the electronics and gradual safe startup
- Solder all the headers to the PCB
- Solder the power modules
- Attach the battery and verify if Raspberry Pi5 boots up
- Solder the startup switch and LED and verify if it can be programmed using a test program
- Attach the motor driver module to the header pins and verify if motors can be controlled using a test program
- Attach the multiplexer module to the header pins and verify if sensors can be read using a test program
- Attach the IMU module to the header pins and verify if orientation values can be read using a test program
- Attach the Raspberry Pi5 wide angle camera

## 6: Download the code
- Connect the Raspberry Pi5 to a monitor, keyboard and mouse
- Install python dependencies
  - `pip3 install adafruit-circuitpython-bno055`
  - `pip3 install adafruit-circuitpython-tca9548a`
  - `pip3 install adafruit-circuitpython-vl53l1x`
- Download the code from the `src` folder to the Raspberry Pi5
- Run the code!
  - `/src/open_challenge/main.py` for Open challenge
  - `/src/obstacle_challenge/main_v3.py` for Obstacle challenge
## 7: Robot stability
- Run the robot and hopefully should run great!
- If the gears make a grinding noise, it is likely due to the lego components not tightly coupled. Use zip ties to ensure the chassis beams are tightly connected.

# Major challenges faced

### Sensor

One major challenge we faced was in working with the VL53L8CX ToF sensor. We have placed it on the back of our robot to aid in parking, but it was extremely unreliable and onerous to work with during testing. The sensor lacked a dedicated Python library (only providing a C-based library), and refused to communicate through our I²C multiplexer. These limitations made integration unexpectedly difficult for us.

To connect this sensor, we first created our own Python version of the C library. Then, we moved the sensor to a secondary I²C bus to bypass the multiplexer and eliminate communication conflicts. 

The sensor failed roughly once in every twenty readings. We wanted to make the sensor more reliable. To solve, this, we went deep into the technical documentation of the sensor and realised that the Raspberry Pi ports were configured as pull down instead of pull ups. Since this fix the sensor has never failed.

### Camera

Another major challenge arose when we tried to use a fish-eye lens in place of our camera for image detection. We wanted to use a fish-eye lens, as it had a wider Field Of View (195 degrees) than our Raspberry Pi Camera Module 3 (120 degrees)

Unfortunately, this didn’t work out. The fish-eye camera has a circular lens, which means all images we received were distorted and circular. This made it difficult to calculate their area, which hindered accuracy. Oftentimes, blocks would be detected either too early or too late. While we could have attempted to add circular ROIs, this would have added significant complexity to the bot and would have required extensive tuning.

# How we used Github

Our team used Github to store all of our code such that it is accessible to all team members and to those who wish to use this repository in the future. We have made frequent commits to this repository, and this repository stands as testament to our efforts, and the process of design as a whole

### The Structure of This Repository

* `t-photos` contains 2 photos of the team (an official one and one funny photo with all team members)
* `v-photos` contains 6 photos of the vehicle (from every side, from top and bottom)
* `video` contains the video.md file with the link to a video where driving demonstration exists
* `schemes` contains several schematic diagrams of the electronic components, chassis, circuit diagram and 3D part images
* `src` contains code of control software for all components which were programmed to participate in the competition
* `models` is for the design files for models used for 3D printing and PCB manufacturing
* `other` is for other files which can be used to understand how to prepare the vehicle for the competition.

### Source code organization

```python
src/
├── motors/
│   ├── motor.py          # DC motor control
│   ├── servo.py          # Servo steering control
│   └── test_pwm.py       # PWM testing
├── sensors/
│   ├── camera.py         # Camera module interface
│   ├── distance.py       # Distance sensor reading
│   ├── bno055.py         # IMU/Gyro sensor
│   ├── color_tuning.py   # Color detection tuning
│   └── vl53l1x.py        # ToF sensor driver
├── open_challenge/
│   ├── main.py           # Open challenge algorithm
│   └── config.py         # Configuration parameters
└── obstacle_challenge/
    ├── main_v3.py        # Obstacle challenge algorithm
    ├── config.py         # Configuration parameters
    └── nationals/        # National competition version
```

### 

# Bill of Materials

| Component | Make and Model | Price | Quantity | Total Price | Component Purchase Link |
|-------------------|--------------------------------|-------|----------|-------------|------------------------|
| Single Board Computer | Raspberry Pi 5 (8GB) | 8291 | 1 | 8291 | https://robu.in/product/raspberry-pi-5-model-8gb/ |
| Camera Module | Raspberry Pi Camera Module 3 | 3551 | 1 | 3551 | https://www.silverlineelectronics.in/products/copy-of-test-1 |
| IMU Sensor | BNO055 9-DOF Intelligent Sensor | 2001 | 1 | 2001 | https://robu.in/product/df-robot-febno055-intelligent-9-axis-sensor-rmion-bno055-intelligent-9-axis-sensor-breakout/ |
| Distance Sensor | VL53L1X ToF Distance Sensor (4-400cm range) | 668 | 1 | 668 | https://robocraze.com/products/vl53l1x-tof-distance-sensor-breakout-with-4-meter-range-7semi |
| Distance Sensor | VL53L8CX ToF Distance Sensor (2-400cm range) | 1892 | 1 | 1892 | https://www.fabtolab.com/pololu-3419-vl53l8cx-time-of-flight-8-8-zone-distance-sensor-carrier-voltage-regulators-400cm-max |
| Distance Sensor | URM09 Ultrasonic Distance Sensor | 1150 | 2 | 2300 | https://wiki.dfrobot.com/URM09_Ultrasonic_Sensor_(Gravity-I2C)_(V1.0)_SKU_SEN0304 |
| I2C Multiplexer | CJMCU TCA9548A 8-Channel I2C Multiplexer | 75 | 1 | 75 | https://robu.in/product/cjmcu-tca9548a-i2c-8-channel-multiple-extensions-development-board/ |
| Servo Motor | TowerPro SG90 9g Mini Servo | 94 | 1 | 94 | https://robu.in/product/towerpro-sg90-9g-mini-servo-9-gram/ |
| Drive Motor | LEGO EV3 Medium Motor | 1500 | 1 | 1500 | https://www.brickowl.com/catalog/lego-mindstorms-ev3-medium-motor-99455 |
| Motor Driver | TB6612FNG Dual Motor Driver Module | 161 | 1 | 161 | https://robu.in/product/motor-driver-tb6612fng-module-performance-ultra-small-volume-3-pi-matching-performance-ultra-l298n/ |
| Battery | Bonka 11.1V 2200mAh 35C LiPo Battery | 1959 | 1 | 1959 | https://www.flyrobo.in/11.1v-2200mah-35c-3s1p-bonka-lipo-battery-bonka-high-capacity-lipo-battery |
| Voltage Converter | XY-3606 24V/12V to 5V 5A Power Module | 160 | 1 | 160 | https://robu.in/product/24v-12v-to-5v-5a-power-module-dc-dc-xy-3606-power-converter/ |
| Mechanical Components | LEGO Mindstorms EV3 (some parts)| 2000 | 1 | 2000 | https://www.brickowl.com/catalog/lego-mindstorms-ev3-set-31313 |
| Differential Gear | LEGO Differential Gear | 150 | 1 | 150 | https://www.brickowl.com/catalog/lego-differential-gear-casing-with-bevel-gear-on-end-with-open-center-62821 |
| Custom PCB | Custom Designed PCB | 6579 | 1 | 6579 | https://www.pcbpower.com/ |
| 3D Printed Parts | Servo mounts, Sensor mount, Camera mounts | 200 | 5 | 1000 |  |
| Total |  |  |  | 32381 | INR |

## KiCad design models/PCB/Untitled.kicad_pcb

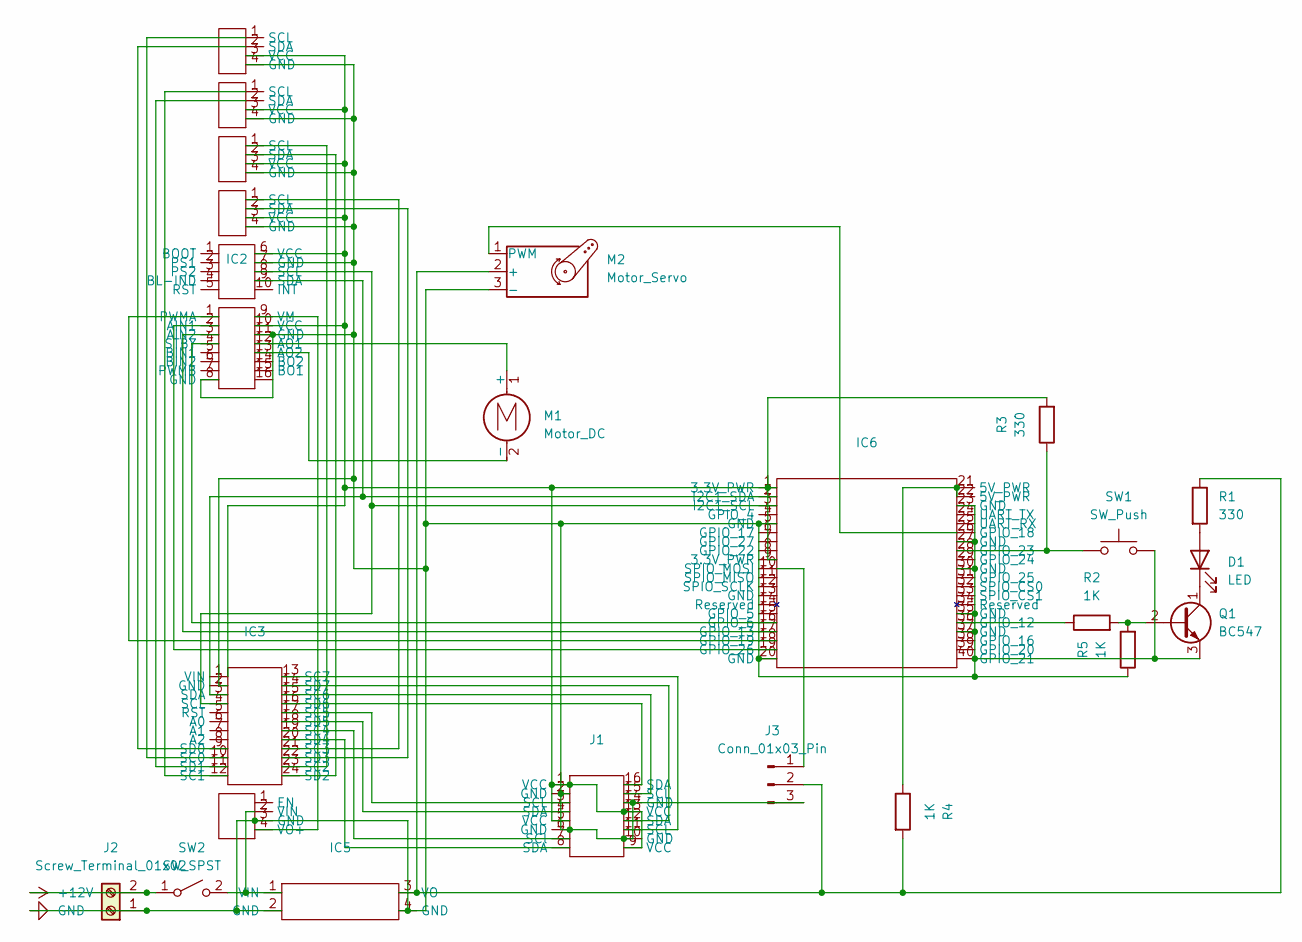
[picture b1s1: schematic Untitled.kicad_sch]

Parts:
D1: LED; LED_D5.0mm
IC1: DFRobot bno005 breakout board
IC2, IC3, IC6: Untitled
IC4: 12v to 9v buck converter
IC5: Untitled_1
J1: Untitled
J2: Screw_Terminal_01x02; TerminalBlock_bornier-2_P5.08mm
J3: Conn_01x03_Pin; PinHeader_1x03_P2.54mm_Vertical
M1: Motor_DC; PinHeader_1x02_P2.54mm_Vertical
M2: Motor_Servo; PinHeader_1x03_P2.54mm_Vertical
Q1: BC547; TO-92_Inline_Wide
R1, R3: 330; R_Axial_DIN0207_L6.3mm_D2.5mm_P10.16mm_Horizontal
R2, R4, R5: 1K; R_Axial_DIN0207_L6.3mm_D2.5mm_P10.16mm_Horizontal
SW1: SW_Push; SW_PUSH-12mm
SW2: SW_SPST; Untitled
U1, U2, U3, U4: VL53l1x; PinSocket_1x04_P2.54mm_Vertical

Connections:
+12V: J2.2, SW2.1 (A)
GND: IC1.7 (GND), IC2.8 (GND), IC2.11 (GND), IC3.2 (GND), IC4.3 (GND), IC5.2 (GND), IC5.4 (GND), IC6.5 (GND), IC6.20 (GND), IC6.23 (GND), IC6.27 (GND), IC6.30 (GND), IC6.35 (GND), IC6.37 (GND), J1.2 (GND), J1.6 (GND), J1.10 (GND), J1.14 (GND), J2.1, J3.3, M2.3 (-), Q1.3 (E), R5.1, SW1.2, U1.4 (GND), U2.4 (GND), U3.4 (GND), U4.4 (GND)
unnamed: D1.2 (A), R1.2
unnamed: D1.1 (K), Q1.1 (C)
unnamed: IC1.8 (SCL), IC3.4 (SCL), IC6.3 (I2C1_SCL)
unnamed: IC1.9 (SDA), IC3.3 (SDA), IC6.2 (I2C1_SDA)
unnamed: IC1.6 (VCC), IC2.10 (VCC), IC3.1 (VIN), IC6.1 (3.3V_PWR), IC6.9 (3.3V_PWR), J1.1 (VCC), J1.5 (VCC), J1.9 (VCC), J1.13 (VCC), R3.2, U1.3 (VCC), U2.3 (VCC), U3.3 (VCC), U4.3 (VCC)
unnamed: IC2.2 (AIN1), IC6.19 (GPIO_26)
unnamed: IC2.3 (AIN2), IC6.17 (GPIO_13)
unnamed: IC2.12 (AO1), M1.1 (+)
unnamed: IC2.13 (AO2), M1.2 (-)
unnamed: IC2.1 (PWMA), IC6.18 (GPIO_19)
unnamed: IC2.4 (STBY), IC6.16 (GPIO_6)
unnamed: IC2.9 (VM), IC4.4 (VO+)
unnamed: IC3.10 (SC0), U1.1 (SCL)
unnamed: IC3.12 (SC1), U2.1 (SCL)
unnamed: IC3.23 (SC2), U3.1 (SCL)
unnamed: IC3.21 (SC3), U4.1 (SCL)
unnamed: IC3.19 (SC4), J1.7 (SCl)
unnamed: IC3.17 (SC5), J1.3 (SCL)
unnamed: IC3.15 (SC6), J1.15 (SCL)
unnamed: IC3.13 (SC7), J1.11 (SCL)
unnamed: IC3.9 (SD0), U1.2 (SDA)
unnamed: IC3.11 (SD1), U2.2 (SDA)
unnamed: IC3.24 (SD2), U3.2 (SDA)
unnamed: IC3.22 (SD3), U4.2 (SDA)
unnamed: IC3.20 (SD4), J1.8 (SDA)
unnamed: IC3.18 (SD5), J1.4 (SDA)
unnamed: IC3.16 (SD6), J1.16 (SDA)
unnamed: IC3.14 (SD7), J1.12 (SDA)
unnamed: IC4.2 (VIN), IC5.1 (VIN), SW2.2 (B)
unnamed: IC5.3 (VO), J3.2, M2.2 (+), R1.1, R4.2
unnamed: IC6.21 (5V_PWR), IC6.22 (5V_PWR), R4.1
unnamed: IC6.36 (GPIO_12), R2.1
unnamed: IC6.26 (GPIO_18), M2.1 (PWM)
unnamed: IC6.28 (GPIO_23), R3.1, SW1.1
unnamed: IC6.10 (SPIO_MOSI), J3.1
unnamed: Q1.2 (B), R2.2, R5.2

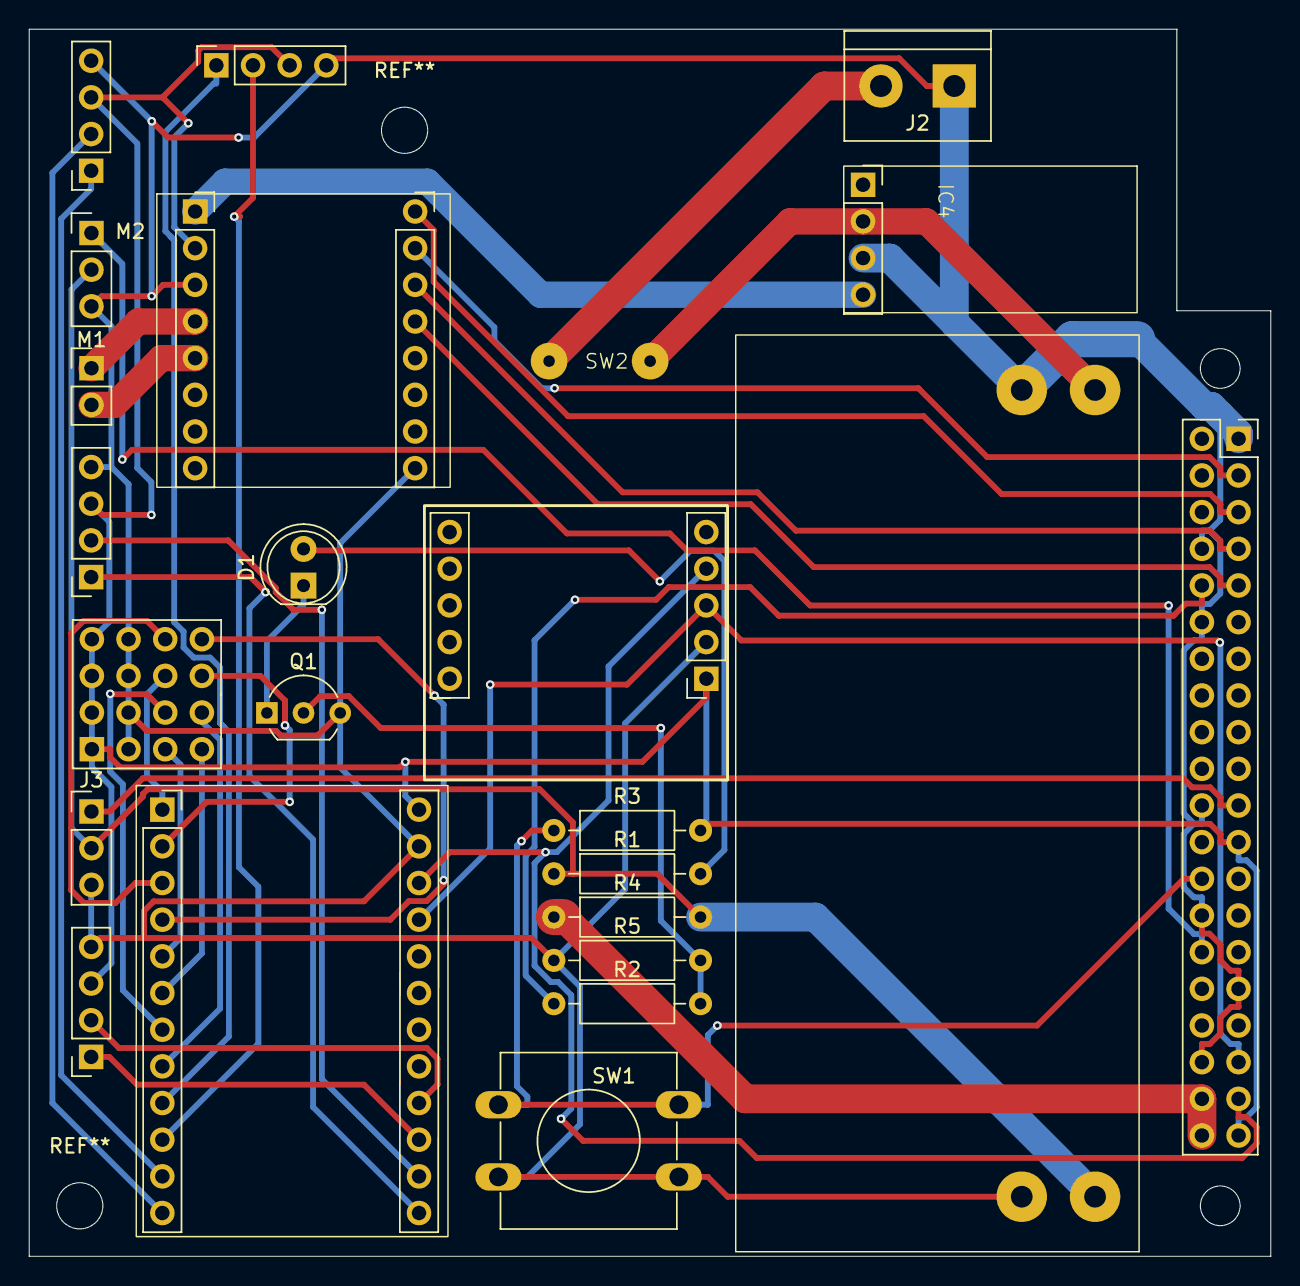
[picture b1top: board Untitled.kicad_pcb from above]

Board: 2 copper layers, 86.0 x 85.0 mm, 24 parts (0 on the bottom side), 38 nets.

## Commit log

2025-07-02 Added WRO FE template
2025-07-02 Added code
2025-07-05 Added relative imports and logic to turn if in corner section
2025-07-17 Created r_photos
2025-07-19 Formatted code and added open_challenge code.
2025-07-19 19/07 Photos
    Rubber Banded Distance Sensor and Camera Hot Glues
2025-08-02 add the logo pic
2025-08-02 added a logo placeholder
2025-08-02 Deleted r_photos
2025-08-02 Added Logo to readme
2025-08-02 Added individual pics placeholder
2025-08-02 Added individual pictures placeholder to README
2025-08-02 Upgraded sensor to vl53l1x, and fixed open_challenge. Added a stop function which stops the robot when tilted for easy stopping.
2025-08-09 Tuned obstacle challenge, does 3 round, no parking. added logic to open challenge to wall follow in start if too close
2025-08-16 added the logo
2025-08-16 Rename greenboticslogo.png to logo.png
2025-08-21 readme updated
2025-08-23 readme updated with more text, sat evening
2025-08-24 Tuned all, obstacle works well, starts from parking. removed unsed code.
2025-08-24 Power and Sense, Mobility, and obstacle completed
2025-08-24 Readme file updated
2025-08-25 ReadME.md updated
2025-08-28 Team photos added
2025-08-28 readme updated with changes
2025-08-31 sunday morning 8am, open, obstacle, parking work well. changed manuver in obstacle complely.
2025-08-31 sunday night 9pm, parking works, obstacle works. added gyro callibration routine, made changes to button press starting up routine.
2025-09-01 Obstacle Challenge Updated
2025-09-02 monday night tuning, issue in red cv. headles added, fixed gyro drift.
2025-09-02 tuesday night, issues in red cv and parking. tested headless.
2025-09-02 Logo Updated
2025-09-02 Changes to readme
2025-09-02 Wiring Diagram Updated
2025-09-02 Wiring Diagram Size Change
2025-09-02 Photo Size Changes
2025-09-03 Final changes made for Document
2025-09-03 wednesday morning, everything works well
2025-10-25 day 1, tuned all
2025-10-25 Major changes to how robot works, primarily using only camera. still in testing phase, src/obstacle_challenge/test2.py contains most of this code
2025-10-29 Tuned for camera module 3, works well. To implment VL53L8CX and parking avoidance and parllel parking
2025-10-30 added logic to avoid hitting parking
2025-10-31 Made logic to get out of parking more robust.
2025-11-02 added vl53l8cx support for back sensor, 3d printed lots of parts of tuned robot
2025-11-06 Made distance functions non blocking and fine tuned parking logic to work reliably in one direction, primarily using camera
2025-11-07 works in lcoskwise parking, all 10 combinations
2025-11-09 tuned getting out of parking in more scenarios
2025-11-09 tuned more possiblities of getting out of parking and made sure turn detection is robust.
2025-11-11 fixed issue where robot crashes into parking, made open challenge code
2025-11-14 Tuned open challenge and cleaned up files
2025-11-14 working for most part, magenta avoidance to be tuned
2025-11-16 Sunday run of obstacle with parking verified with 20 variations
2025-11-17 Sleep removal in parking logic
2025-11-19 changed servo back to sg90 as mg90 burnt. Tuned for sg90 and optimized parking manuver
2025-11-20 Tuned parking in multiple scenarios and added timeout in certain parking parts to ensure robot is not stuck
2025-11-21 Improving sensor reliability
2025-11-21 More sensor reliability changes
2025-11-21 Fixing IMU stability due to sensor reinitialisation
2025-11-21 fixing errors
2025-11-21 fixed thread not stoping
2025-11-22 performance optimization
2025-11-22 File renaming
2025-11-24 Parking tuning and LAB support
2025-11-24 Final commit before leaving India
2025-11-24 Implement arena and robot simulation in open_challenge.m
    Added arena geometry, robot setup, and simulation logic for a rectangular path with car-like turns and wiggle effect.
2025-11-24 Updated documentation
2025-11-24 Adding png files
2025-11-25 Adding Table of Contents
2025-11-25 Revise image formatting and video playlist link
    Updated image tags and descriptions in the README.
2025-11-25 Update video.md with new video links
    Added multiple YouTube video links and a playlist link.
2025-11-25 Expand README with more schematic diagrams
    Added additional schematic diagrams and images for various components.
2025-11-26 Enhance README with project overview and instructions
    Expanded README to include project details, layout, dependencies, installation instructions, and usage.
2025-11-28 day one
